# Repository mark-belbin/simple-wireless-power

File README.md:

# Simple Wireless Power System

## Introduction 
This project is a simple two-board wireless power system that can transmit up to 100W at close distances. Originally it was designed as a small part of a subsea resident autonomous underwater vehicle senior design project. The goal was to have a contactless method to charge the vehicles battery in an underwater docking station, versus a contact method like a wetmate connector. This reduces the chance for failure in a harsh ocean environment. Included in this repository are schematics, PCB design files, LTspice simulations, and embedded code.

## Design Topology
At the start of my wireless power investigation, it was initially decided to create a type of "coreless transformer" to keep things simple. This type of design would transfer power by simply placing two identical coils as close as possible to each other. The closer the coils, the higher their mutal inductance and coupling coefficient. The coupling coefficient directly equals the maximum achievable efficiency; k=0.7 would mean 70% efficiency for example. 

> Coreless transformer equivalent circuit.

However, since a lot of work was already being placed into research and simulation anyways, it was decided to try and create a resonant system. Using capactiors, resonant circuits can be created with the inductive transmitter and reciever coils, increasing efficiency accross the wireless link. This is the de facto inductive wireless power transfer method used in industry, and it turned out to be simpler than thought. The topology chosen is called "series-series" resonant inductive wireless power transfer, which means that the compensating capacitors are placed in series with both the transmit and recieve coils. Other topologys exist such as "series-parallel" or "parallel-parallel" which place the capacitors in parallel with the coils as well.

> Series-series topology circuit.

## Hardware
The system consists of a transmitter (TX) PCB and a reciever (RX) PCB. Both are 4 layer 1oz copper boards that are 100x45mm. The designs were completed using KiCAD EDA (http://kicad-pcb.org/), a free and open source PCB design software that is highly recommended. 

### TX Board
The transmitter board's primary purpose is to take a DC input voltage and pass it through a full bridge inverter to create a high frequency sinusoidal voltage. This sinusoidal voltage passes through the compensating capacitors and transmitter coil, and creates an alternating magnetic field that couples to the reciever coil. The H-Bridge is designed around an operating point of 24VDC input, 100kHz switching frequency, and up to 100W of transfer power. The main limiter for power transfer is the rated voltage and current of the coils and compensating capacitors. The MOSFETs of the H-Bridge are over-speced to minimize losses. Short circuit protection circuitry is included on the TX board, since if the TX coil is open-loaded during operation it will appear as a short to the input power supply.

The TX board also has an embedded SAMD21 microntroller which generates the nessecary PWM signal for the gate drivers. Further, the board includes a CAN controller and transceiver so that it could potentially be commanded on/off and relay power transfer telemetry to a remote control computer via CANBus.

### RX Board
The RX board is much simpler than the TX board. It has no microcontroller, and uses passive schottky diodes in a full bridge rectifier configuration to convert the recieved AC voltage back to a usable DC voltage. An simple overvoltage protection scheme is incorporated in the RX board to prevent an overvoltage event downstream. A schmitt trigger circuit watches the output voltage, and if it is too high, connects the output to a bank of bleeder resistors. The extra load on the output subsequently draws down the voltage before it reaches a harmful level. 
                                                                                   

### Key Components

#### Coils
The transmitter and reciever coils are identical. They were sourced on Digi-Key from Wurth Electronics, PN 732-9670-ND. They have an inductance of 5.8uH, and a very low series resistance, allowing for high current rating. I think these are probably the highest current rated coils you can find on Digikey when I selected them! As well, Wurth was kind enough to provide ample documentation for the coils. A key piece of data was a graph of their Quality factor (Q) versus frequency. The higher the quality factor, the better the efficiency. Therefore, since the Q peaked at around 100-101kHz, that was the selected operating frequency for the entire system.

> Coils encased and epoxyed in a custom mount for underwater use in the original AUV application. 

#### Series Capacitors
Four 100nF capacitors were placed in parallel to achieve the desired ~380-400nF series capacitance. Large 2220 package ceramic capacitors were chosen for their desirable low series resistance. The final parts were chosen from Murata Electronics and sourced on Digikey, PN 490-16696-1-ND. These capacitors were compared against others, again looking at their quality factor over frequency. The series capacitors ended up being the weakest link in the system, and would fail on the TX side when delivering over 5-6A. These caps had the best that could be found at the time, but if someone knows of a better or higher current-carrying choice, let me know! 

#### MOSFETs
The MOSFETs chosen are low-loss N-Channel devices. The final parts chosen are from Infineon and sourced on Digi-Key, PN 448-IAUC70N08S5N074ATMA1CT-ND. These FETs were selected for the lowest possible loss, taking into account both resistive and switching losses. 

#### Diodes
The diodes for the full-bridge rectifier were chosen again for as low of loss as possible. Really, the low voltage and high current environment is probably better suited for active rectification, but to keep things simple passive rectification was chosen. The best diodes for this are schottky due to their low forward voltage. The final parts chosen are from ON Semi and sourced from Digi-Key, PN FSV12100VCT-ND. A few different diode models were selected and simulated in the final circuit, and this model ended up producing the lowest loss. 

#### Micro Controller
The chosen microcontroller is the SAMD21G18A, PN ATSAMD21G18A-MF-ND. This is the same microcontroller that is on the Arduino Zero dev board, and our senior design team already knew how to easily program and flash it. Perhaps someone could modify this design and retrofit a more popular microcontroller, like an STM32.

## Software
The current software developed for this project is the embedded code on the TX board's SAMD21 microcontroller. Code was developed using the Arduino IDE for simplicity. A .bin file was generated and then uploaded to the microcontroller using a J-Link EDU programmer. The code is about as simple as it gets, just generating a 50% duty cycle, 100kHz PWM signal. No feedback is incorporated since it is assumed that there is no expected communication between TX and RX boards in the original underwater application. 

## Simulation
The entire end-to-end wireless power system was simulated in LTspice. The simulation aided in component selection, and gave an initial estimate of efficiency greater than 90%. It's hard to say how accurate the simulation is, since it's not clear what coupling factor, k, will be present in a real world system. Any tips on WPT system simulation in LTspice would be greatly appreciated! 

## Testing Results
The system was tested with surpising results. At a gap distance of about 1-2mm, as close as we could get, the system was able to transfer power up to 100W at an efficiency of 81.3%. Testing different frequencies between 95-105kHz did not show any noticeable difference in efficiency. The coils were also submerged in saltwater to check efficiency versus the in-air test. There was no measurable difference in water, salt or fresh.

Another interesting outcome was shown in the thermal images during testing. The hottest components in the system were the series capacitors, reaching upwards of 70C degrees after 5 mins of operation. No heatsink or airflow meant that these are probably worst case numbers, but still perhaps the capacitors could be underspec'd for the application. At 100W delivered, about 20W is lost in the system, and the series capacitors are the only noticeable components that heat up significantly. It's a bit inconcievable that all the 20W is split amongst 8 small capacitors, so I assume that there are some losses in the surrounding air that are radiated away. It's hard to tell, would definitely be open to some insight on this if anyone has encountered this before! 

Efficiency vs coil gap distance measurements were completed with some interesting results. First, efficiency seems to drop linearly from 0-20mm. This is cool since it seems that the resonant effect is indeed working. Normally a magnetic field would decrease with the distance squared, a non-linear relationship. As well, when reaching 20mm or beyond, the TX board was limited by its series current capability. More series current is required in to the transmitter coil to achieve the same power transfer as efficiency drops. The series capacitors on the TX board were the limiter, as they started to fail beyond 6A. A heatsink and forced air could give them a bit of extra capability potentially. I'd be interested in hearing about any better capacitor choices for higher series current while maintaining low loss accross them, or perhaps if a parallel-series or parallel-parallel topology would solve this problem.

## Discussion
This was a fun project and a small part of a much larger senior design project. 80-75% efficiency for 0-5mm coil gap satisfies the original design problem, which was to safely deliver 50W underwater at a 0-5mm gap distance. Always open for discussion or any tips on how this could have been done better. For a future project I'm interested in trying to make a super small low power version that could deliver 5-10W for underwater sensor applications.

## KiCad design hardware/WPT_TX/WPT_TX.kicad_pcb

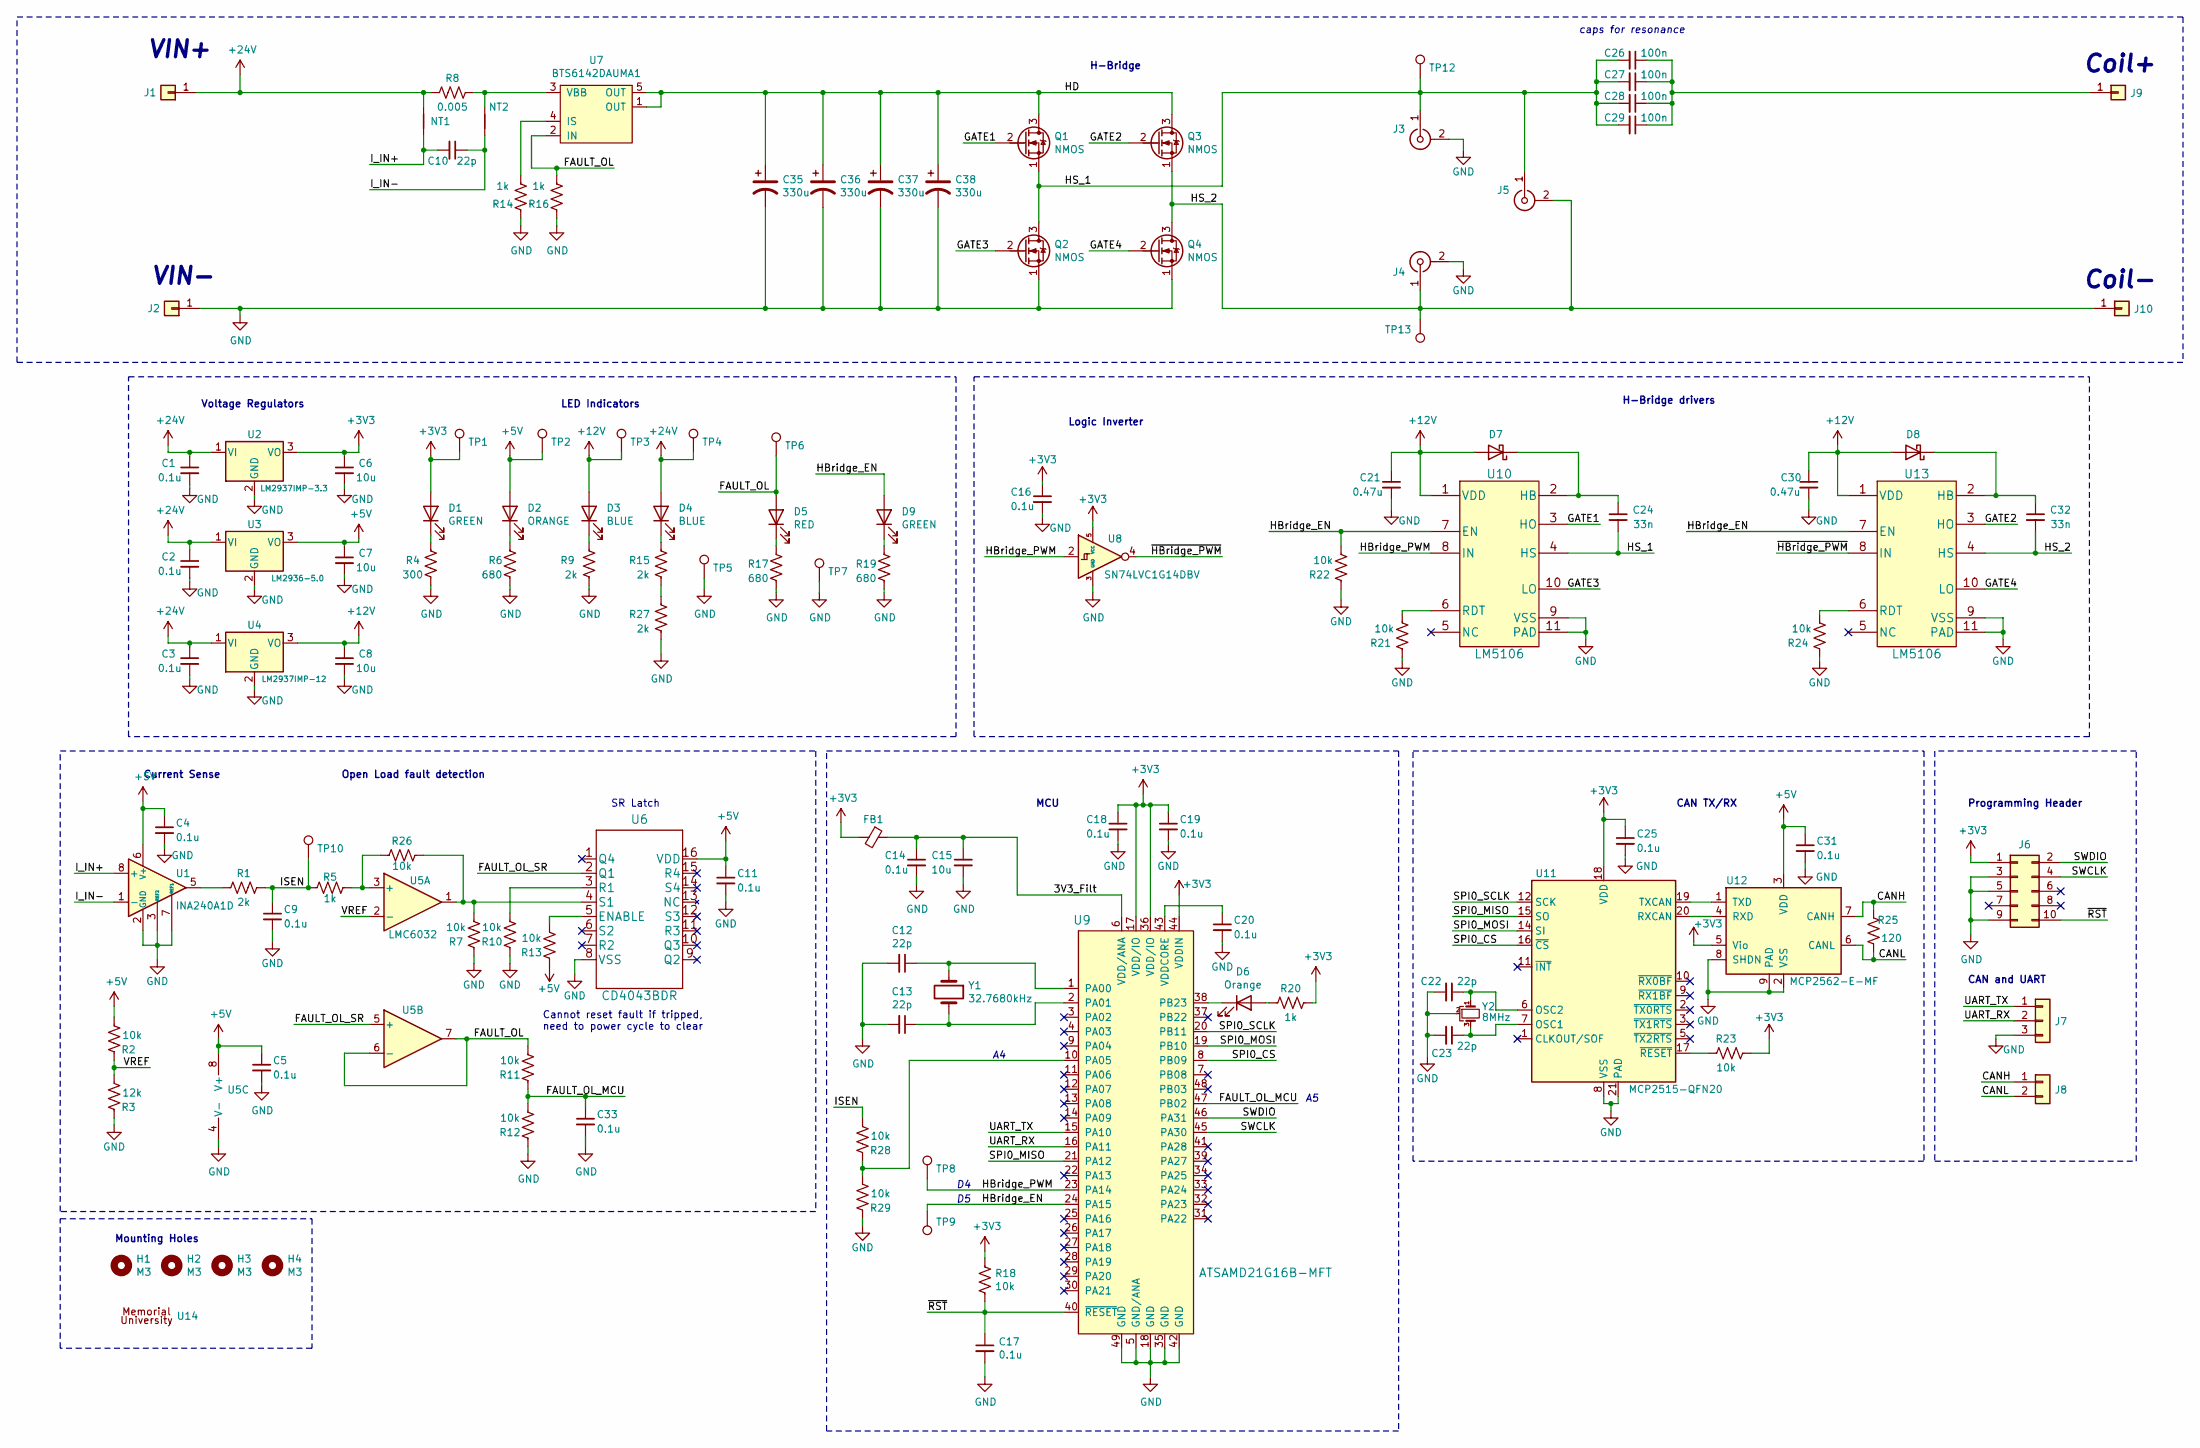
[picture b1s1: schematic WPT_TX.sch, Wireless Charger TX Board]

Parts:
C1, C2, C3: 0.1u; C_0603_1608Metric; Digikey 1276-1941-1-ND
C4, C5, C9, C11, C14, C16, C17, C18, C19, C20, C25, C31, C33: 0.1u; C_0603_1608Metric; Digikey 1276-1258-1-ND
C6, C7, C8: 10u; C_1206_3216Metric; Digikey 1276-6767-1-ND
C10, C12, C13, C22, C23: 22p; C_0603_1608Metric; Digikey 720-VJ0603A220JXBACCT-ND
C15: 10u; C_0603_1608Metric; Digikey 490-7201-1-ND
C21, C30: 0.47u; C_0805_2012Metric; Digikey 478-10438-1-ND
C24, C32: 33n; C_0805_2012Metric; Digikey 445-172691-1-ND
C26, C27, C28, C29: 100n; C_2220_5650Metric; Digikey 490-16696-1-ND
C35, C36, C37, C38: 330u; CP_Elec_10x12.5; Digikey 493-13765-1-ND
D1, D9: GREEN; LED_0805_2012Metric; Digikey 160-1423-1-ND
D2: ORANGE; LED_0805_2012Metric; Digikey 160-1413-1-ND
D3, D4: BLUE; LED_0805_2012Metric; Digikey 160-1579-1-ND
D5: RED; LED_0805_2012Metric; Digikey 475-1415-1-ND
D6: Orange; LED_0805_2012Metric; Digikey 160-1413-1-ND
D7, D8: D_Schottky; D_SOD-323_HandSoldering; Digikey 641-1786-1-ND
FB1: FB; L_0805_2012Metric; Digikey 490-9706-1-ND
H1, H2, H3, H4: M3; MountingHole_3.2mm_M3_DIN965_Pad
J1, J2, J9, J10: Conn_01x01; SolderWirePad_single_SMD_5x10mm
J3, J4, J5: Conn_Coaxial; SMA_Amphenol_901-144_Vertical; Digikey WM17068-ND
J6: Conn_02x05_Odd_Even; PinHeader_2x05_P1.27mm_Vertical; Digikey 1175-1627-ND
J7: Conn_01x03; 70553-03; Digikey WM4154-ND
J8: Conn_01x04; 70553-02; Digikey WM4900-ND
NT1, NT2: Net-Tie_2; NetTie-2_SMD_Pad0.25mm
Q1, Q2, Q3, Q4: NMOS; TDSON-8-1; Digikey 448-IAUC70N08S5N074ATMA1CT-ND
R1, R9, R15, R27: 2k; R_0603_1608Metric; Digikey 541-2790-1-ND
R2, R7, R10, R11, R12, R13, R18, R21, R22, R23, R24, R26, R28, R29: 10k; R_0603_1608Metric; Digikey RHM10KDCT-ND
R3: 12k; R_0603_1608Metric; Digikey P12KDBCT-ND
R4: 300; R_0603_1608Metric; Digikey P300BZCT-ND
R5, R14, R16, R20: 1k; R_0603_1608Metric; Digikey RHM1.0KDCT-ND
R6, R17, R19: 680; R_0603_1608Metric; Digikey RHM680DCT-ND
R8: 0.005; R_2512_Sense; Digikey YAG6124CT-ND
R25: 120; R_0603_1608Metric; Digikey P120BYTR-ND
TP1, TP2, TP3, TP4: TestPoint; TestPoint_Loop_D1.80mm_Drill1.0mm_Beaded; Digikey 36-5000-ND
TP5, TP6, TP7: TestPoint; TestPoint_Loop_D1.80mm_Drill1.0mm_Beaded; Digikey 36-5001-ND
TP8, TP9, TP10, TP12, TP13: TestPoint; TestPoint_Loop_D1.80mm_Drill1.0mm_Beaded; Digikey 36-5117-ND
U1: INA240A1D; SOIC-8_3.9x4.9mm_P1.27mm; Digikey 296-48837-ND
U2: LM2937IMP-3.3; SOT-223-3_TabPin2; Digikey LM2937IMPX-3.3/NOPBCT-ND
U3: LM2936-5.0; SOT-223-3_TabPin2; Digikey 296-37374-1-ND
U4: LM2937IMP-12; SOT-223-3_TabPin2; Digikey LM2937IMP-12/NOPBCT-ND
U5: LMC6032; SOIC-8_3.9x4.9mm_P1.27mm
U6: CD4043BDR; SOIC-16_3.9x9.9mm_P1.27mm; Digikey 296-31496-1-ND
U7: BTS6142DAUMA1; TO-252-4; Digikey BTS6142DAUMA1CT-ND
U8: SN74LVC1G14DBV; TSOT-23-5; Digikey 296-35944-1-ND
U9: ATSAMD21G16B-MFT; QFN-48-1EP_7x7mm_P0.5mm_EP5.6x5.6mm; Digikey ATSAMD21G18A-MF-ND
U10, U13: LM5106; LM5106SD; Digikey LM5106SD/NOPBCT-ND
U11: MCP2515-QFN20; QFN-20-1EP_4x4mm_P0.5mm_EP2.5x2.5mm_ThermalVias; Digikey MCP2515-E/ML-ND
U12: MCP2562-E-MF; DFN-8-1EP_3x3mm_P0.65mm_EP1.55x2.4mm; Digikey MCP2562-E/MF-ND
U14: Munlogo; MUNLOGO
Y1: 32.7680kHz; Crystal_SMD_3215-2pin_3.2x1.5mm; Digikey ‎XC1656CT-ND‎
Y2: 8MHz; OSCCC320X250; Digikey 2151-RH100-8.000-20-3050-EXT-TRCT-ND

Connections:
+3V3: C6.1, C16.1, C18.1, C19.1, C25.1, D1.2 (A), FB1.2, J6.1, R18.1, R20.1, R23.1, TP1.1, U2.3 (VO), U8.5 (VCC), U9.17 (VDD/IO), U9.36 (VDD/IO), U9.44 (VDDIN), U11.18 (VDD), U12.5 (Vio)
+5V: C4.1, C5.1, C7.1, C11.1, C31.1, D2.2 (A), R2.2, R13.1, TP2.1, U1.6 (V+), U3.3 (VO), U5.8 (V+), U6.16 (VDD), U12.3 (VDD)
+12V: C8.1, C21.1, C30.1, D3.2 (A), D7.2 (A), D8.2 (A), TP3.1, U4.3 (VO), U10.1 (VDD), U13.1 (VDD)
+24V: C1.1, C2.1, C3.1, D4.2 (A), J1.1, NT1.1, R8.2, TP4.1, U2.1 (VI), U3.1 (VI), U4.1 (VI)
/3V3_Filt: C14.1, C15.1, FB1.1, U9.6 (VDD/ANA)
/CANH: J8.1, R25.2, U12.7 (CANH)
/CANL: J8.2, R25.1, U12.6 (CANL)
/FAULT_OL: D5.2 (A), R11.2, R16.2, TP6.1, U5.6 (-), U5.7, U7.2 (IN)
/FAULT_OL_MCU: C33.1, R11.1, R12.2, U9.47 (PB02)
/FAULT_OL_SR: U5.5 (+), U6.2 (Q1)
/GATE1: Q1.2 (G), U10.3 (HO)
/GATE2: Q3.2 (G), U13.3 (HO)
/GATE3: Q2.2 (G), U10.10 (LO)
/GATE4: Q4.2 (G), U13.10 (LO)
/HBridge_EN: D9.2 (A), R22.2, TP9.1, U9.24 (PA15), U10.7 (EN), U13.7 (EN)
/HBridge_PWM: TP8.1, U8.2, U9.23 (PA14), U10.8 (IN)
/HD: C35.1, C36.1, C37.1, C38.1, Q1.3 (D), Q3.3 (D), U7.1 (OUT), U7.5 (OUT)
/HS_1: C24.2, C26.2, C27.2, C28.2, C29.2, J3.1 (In), J5.1 (In), Q1.1 (S), Q2.3 (D), TP12.1, U10.4 (HS)
/HS_2: C32.2, J4.1 (In), J5.2 (Ext), J10.1, Q3.1 (S), Q4.3 (D), TP13.1, U13.4 (HS)
/ISEN: C9.1, R1.1, R5.2, R28.2, TP10.1
/I_IN+: C10.2, NT1.2, U1.8 (+)
/I_IN-: C10.1, NT2.1, U1.1 (-)
/SPI0_CS: U9.8 (PB09), U11.16 (~CS)
/SPI0_MISO: U9.21 (PA12), U11.15 (SO)
/SPI0_MOSI: U9.19 (PB10), U11.14 (SI)
/SPI0_SCLK: U9.20 (PB11), U11.12 (SCK)
/SWCLK: J6.4, U9.45 (PA30)
/SWDIO: J6.2, U9.46 (PA31)
/UART_RX: J7.2, U9.16 (PA11)
/UART_TX: J7.1, U9.15 (PA10)
/VREF: R2.1, R3.2, U5.2 (-)
/~HBridge_PWM~: U8.4, U13.8 (IN)
/~RST~: C17.1, J6.10, R18.2, U9.40 (~RESET)
GND: C1.2, C2.2, C3.2, C4.2, C5.2, C6.2, C7.2, C8.2, C9.2, C11.2, C12.2, C13.2, C14.2, C15.2, C16.2, C17.2, C18.2, C19.2, C20.2, C21.2, C22.2, C23.2, C25.2, C30.2, C31.2, C33.2, C35.2, C36.2, C37.2, C38.2, J2.1, J3.2 (Ext), J4.2 (Ext), J6.3, J6.5, J6.9, J7.3, Q2.1 (S), Q4.1 (S), R3.1, R4.1, R6.1, R7.1, R9.1, R10.1, R12.1, R14.1, R16.1, R17.1, R19.1, R21.1, R22.1, R24.1, R27.1, R29.1, TP5.1, TP7.1, U1.2 (GND), U1.3 (REF2), U1.4 (GND), U1.7 (REF1), U2.2 (GND), U3.2 (GND), U4.2 (GND), U5.4 (V-), U6.8 (VSS), U8.3 (GND), U9.5 (GND/ANA), U9.18 (GND), U9.35 (GND), U9.42 (GND), U9.49 (GND), U10.9 (VSS), U10.11 (PAD), U11.8 (VSS), U11.21 (PAD), U12.2 (VSS), U12.8 (SHDN), U12.9 (PAD), U13.9 (VSS), U13.11 (PAD), Y2.2
unnamed: C12.1, U9.1 (PA00), Y1.1
unnamed: C13.1, U9.2 (PA01), Y1.2
unnamed: C20.1, U9.43 (VDDCORE)
unnamed: C22.1, U11.6 (OSC2), Y2.1
unnamed: C23.1, U11.7 (OSC1), Y2.3
unnamed: C24.1, D7.1 (K), U10.2 (HB)
unnamed: C26.1, C27.1, C28.1, C29.1, J9.1
unnamed: C32.1, D8.1 (K), U13.2 (HB)
unnamed: D1.1 (K), R4.2
unnamed: D2.1 (K), R6.2
unnamed: D3.1 (K), R9.2
unnamed: D4.1 (K), R15.2
unnamed: D5.1 (K), R17.2
unnamed: D6.1 (K), U9.38 (PB23)
unnamed: D6.2 (A), R20.2
unnamed: D9.1 (K), R19.2
unnamed: NT2.2, R8.1, U7.3 (VBB)
unnamed: R1.2, U1.5
unnamed: R10.2, U6.3 (R1)
unnamed: R13.2, U6.5 (ENABLE)
unnamed: R14.2, U7.4 (IS)
unnamed: R15.1, R27.2
unnamed: R21.2, U10.6 (RDT)
unnamed: R23.2, U11.17 (~RESET)
unnamed: R24.2, U13.6 (RDT)
unnamed: R7.2, R26.1, U5.1, U6.4 (S1)
unnamed: R5.1, R26.2, U5.3 (+)
unnamed: R28.1, R29.2, U9.10 (PA05)
unnamed: U11.19 (TXCAN), U12.1 (TXD)
unnamed: U11.20 (RXCAN), U12.4 (RXD)

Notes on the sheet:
Coil+
VIN+
VIN-
Coil-
caps for resonance
Current Sense
Open Load fault detection
Voltage Regulators
MCU
CAN TX/RX
H-Bridge
H-Bridge drivers
Cannot reset fault if tripped, need to power cycle to clear
SR Latch
Logic Inverter
Programming Header
CAN and UART
LED Indicators
Mounting Holes

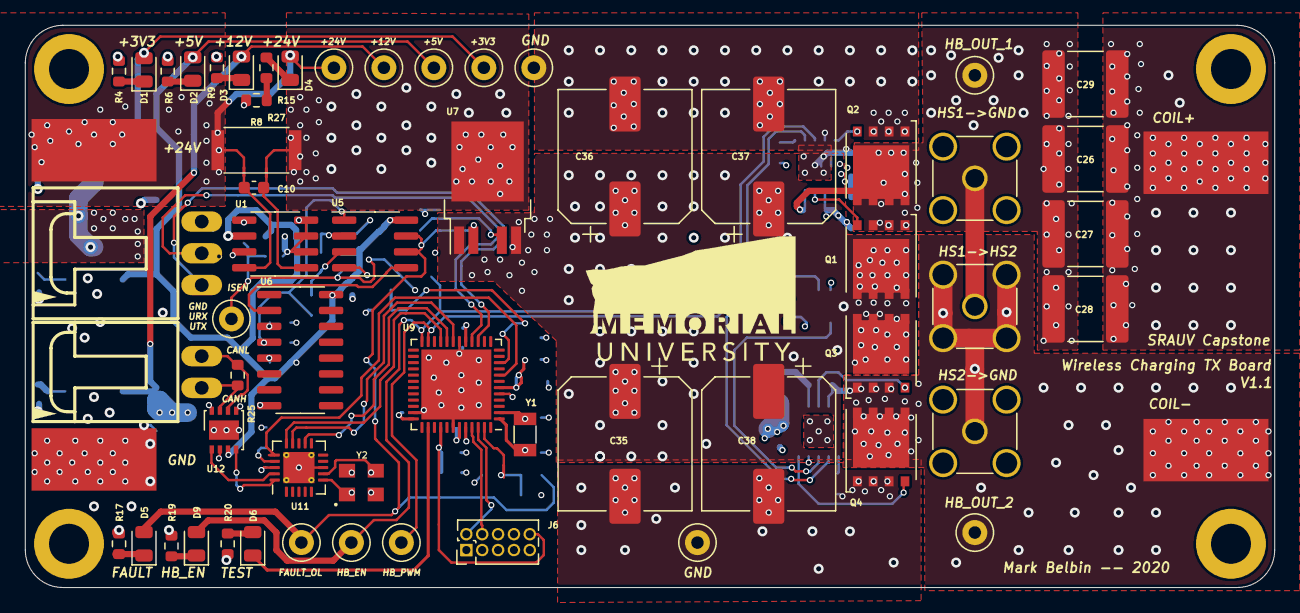
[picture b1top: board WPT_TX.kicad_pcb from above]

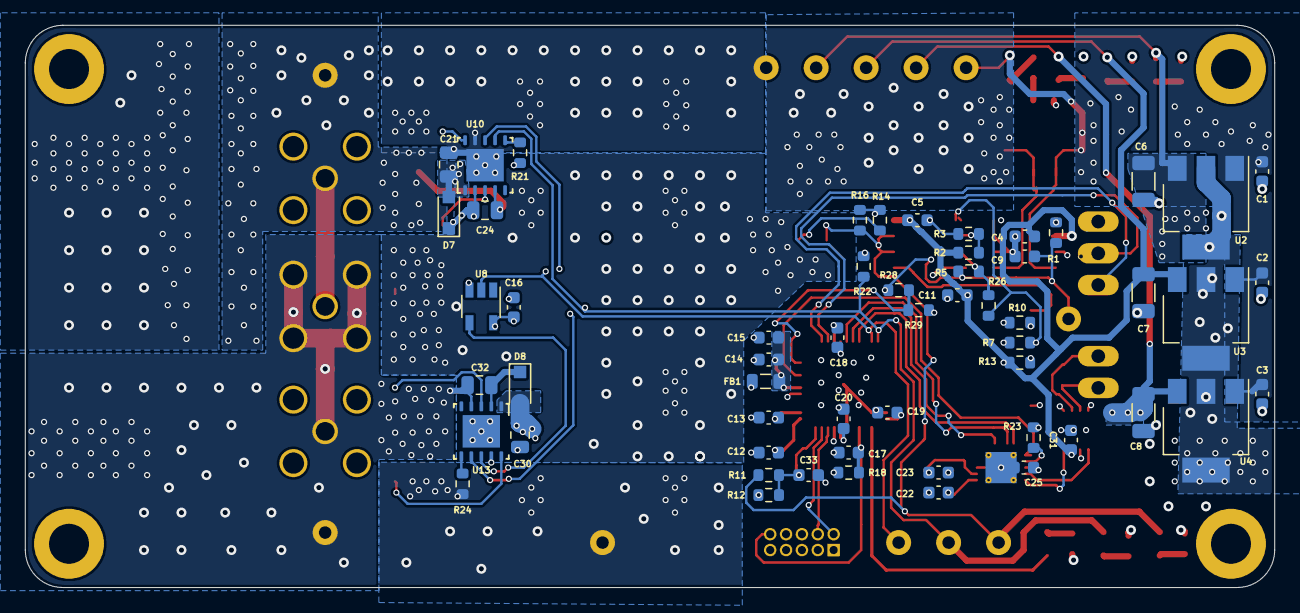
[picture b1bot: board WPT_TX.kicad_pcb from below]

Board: 4 copper layers, 100.0 x 45.0 mm, 124 parts (56 on the bottom side), 64 nets.

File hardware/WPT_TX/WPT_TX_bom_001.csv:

Component,Description,Part,References,Value,Footprint,Quantity Per PCB,Datasheet,Digikey
1,"Unpolarized capacitor, small symbol",C_Small,C1 C2 C3 C4 C5 C9 C11 C14 C16 C17 C18 C19 C20 C25 C31 C33,0.1u,C_0603_1608Metric,16,~,1276-1941-1-ND 1276-1258-1-ND
2,"Unpolarized capacitor, small symbol",C_Small,C21 C30,0.47u,C_0805,2,~,478-10438-1-ND
3,"Unpolarized capacitor, small symbol",C_Small,C26 C27 C28 C29,100n,C_2220,4,~,490-16696-1-ND
4,"Unpolarized capacitor, small symbol",C_Small,C15,10u,C_0603_1608Metric,1,~,490-7201-1-ND
5,"Unpolarized capacitor, small symbol",C_Small,C6 C7 C8,10u,C_1206,3,~,1276-6767-1-ND
6,"Unpolarized capacitor, small symbol",C_Small,C10 C12 C13 C22 C23,22p,C_0603_1608Metric,5,~,720-VJ0603A220JXBACCT-ND
7,"Unpolarized capacitor, small symbol",C_Small,C24 C32,33n,C_0805,2,~,445-172691-1-ND
8,Light emitting diode,LED,D3 D4,BLUE,LED_0805_2012Metric,2,~,160-1579-1-ND
9,Schottky diode,D_Schottky,D7 D8,D_Schottky,D_SMA,2,~,SS16T3GOSCT-ND
10,Light emitting diode,LED,D1 D9,GREEN,LED_0805_2012Metric,2,~,160-1423-1-ND
11,Light emitting diode,LED,D2 D6,ORANGE,LED_0805_2012Metric,2,~,160-1413-1-ND
12,Light emitting diode,LED,D5,RED,LED_0805_2012Metric,1,~,475-1415-1-ND
13,"Ferrite bead, small symbol",Ferrite_Bead_Small,FB1,FB,L_0805_2012Metric,1,~,490-9706-1-ND
14,"Generic connector, single row, 01x01, script generated (kicad-library-utils/schlib/autogen/connector/)",Conn_01x01,J1 J2 J9 J10,Conn_01x01,SolderWirePad_single_SMD_5x10mm,4,~,
15,"Generic connector, single row, 01x03, script generated (kicad-library-utils/schlib/autogen/connector/)",Conn_01x03,J7,Conn_01x03,70553-03,1,~,WM4154-ND
16,"Generic connector, single row, 01x02, script generated (kicad-library-utils/schlib/autogen/connector/)",Conn_01x02,J8,Conn_01x04,70553-02,1,~,WM4900-ND
17,"Generic connector, double row, 02x05, odd/even pin numbering scheme (row 1 odd numbers, row 2 even numbers), script generated (kicad-library-utils/schlib/autogen/connector/)",Conn_02x05_Odd_Even,J6,Conn_02x05_Odd_Even,Pin_Header_Straight_2x05_Pitch1.27mm,1,~,1175-1627-ND
18,"coaxial connector (BNC, SMA, SMB, SMC, Cinch/RCA, ...)",Conn_Coaxial,J3 J4 J5,Conn_Coaxial,SMA_Amphenol_901-144_Vertical,3, ~,WM17068-ND
19,"Net tie, 2 pins",Net-Tie_2,NT1 NT2,Net-Tie_2,NetTie-2_SMD_Pad0.25mm,2,~,
20,"N-MOSFET transistor, source/gate/drain",Q_NMOS_SGD,Q1 Q2 Q3 Q4,NMOS,TDSON-8-1,4,https://www.infineon.com/dgdl/Infineon-IAUC70N08S5N074-DS-v0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,448-IAUC70N08S5N074ATMA1CT-ND
21,"Resistor, US symbol",R_US,R8,0.005,R_2512_Sense,1,~,YAG6124CT-ND
22,"Resistor, US symbol",R_US,R3 R7 R10 R11 R12 R13 R18 R21 R22 R23 R24 R26,10k,R_0603_1608Metric,12,~,RHM10KDCT-ND
23,"Resistor, US symbol",R_US,R25,120,R_0603_1608Metric,1,~,P120BYTR-ND
24,"Resistor, US symbol",R_US,R9 R14 R16 R20,1k,R_0603_1608Metric,4,~,RHM1.0KDCT-ND
25,"Resistor, US symbol",R_US,R1 R15,2k,R_0603_1608Metric,2,~,541-2790-1-ND
26,"Resistor, US symbol",R_US,R4,330,R_0603_1608Metric,1,~,RHM330DCT-ND
27,"Resistor, US symbol",R_US,R6 R17 R19,680,R_0603_1608Metric,3,~,RHM680DCT-ND
28,"Resistor, US symbol",R_US,R2 R5,79.6k,R_0603_1608Metric,2,~,13-RT0603BRD0779K6LCT-ND
29,IC MCU 32BIT 64KB FLASH 48QFN,ATSAMD21G16B-MFT,U9,ATSAMD21G16B-MFT,TQFP-48_7x7mm,1,http://www.microchip.com/mymicrochip/filehandler.aspx?ddocna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,ATSAMD21G18A-MF-ND
30,,BTS6142DAUMA1,U7,BTS6142DAUMA1,TO-252-4,1,https://www.infineon.com/dgdl/Infineon-BTS6142D-DS-v01_01-EN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,BTS6142DAUMA1CT-ND
31,,CD4043BDR,U6,CD4043BDR,SOIC-16_3.9x9.9mm_Pitch1.27mm,1,,296-31496-1-ND
32,"High- and Low-Side, Bidirectional, Zero-Drift, Current-Sense Amplifier With Enhanced PWM Rejection, 20V/V, SOIC-8",INA240A1D,U1,INA240A1D,SOIC-8_3.9x4.9mm_P1.27mm,1,http://www.ti.com/lit/ds/symlink/ina240.pdf,296-48837-ND
33,"50mA Ultra-Low Quiescent Current LDO Voltage Regulator, 5.0V fixed output, TO-252/SOT-223",LM2936-5.0,U3,LM2936-5.0,SOT-223-3_TabPin2,1,http://www.ti.com/lit/ds/symlink/lm2936.pdf,296-37374-1-ND
34,"500-mA Low Dropout Regulator, SOT-223",LM2937xMP,U4,LM2937IMP-12,SOT-223-3_TabPin2,1,http://www.ti.com/lit/ds/symlink/lm2937.pdf,LM2937IMP-12/NOPBCT-ND
35,"500-mA Low Dropout Regulator, SOT-223",LM2937xMP,U2,LM2937IMP-3.3,SOT-223-3_TabPin2,1,http://www.ti.com/lit/ds/symlink/lm2937.pdf,LM2937IMPX-3.3/NOPBCT-ND
36,,LM5106SD_NOPB,U10 U13,LM5106,LM5106SD,2,,LM5106SD/NOPBCT-ND
37,"Precision CMOS Dual Operational Amplifier, DIP-8/SOIC-8",LMC6082,U5,LMC6032,SOIC-8_3.9x4.9mm_Pitch1.27mm,1,http://www.ti.com/lit/ds/symlink/lmc6082.pdf,296-49646-1-ND
38,,MCP2515-QFN20,U11,MCP2515-QFN20,TSSOP-20_4.4x6.5mm_P0.65mm,1,,MCP2515-E/ML-ND
39,"High-Speed CAN Transceiver, 1Mbps, 5V supply, Vio pin, -40C to +125C, DFN-8",MCP2562-E-MF,U12,MCP2562-E-MF,DFN-8-1EP_3x3mm_P0.65mm_EP1.55x2.4mm,1,http://ww1.microchip.com/downloads/en/DeviceDoc/25167A.pdf,MCP2562-E/MF-ND
40,"Single Schmitt-Trigger Inverter, SOT-23",SN74LVC1G14DBV,U8,SN74LVC1G14DBV,SOT-23-5,1,http://www.ti.com/lit/ds/symlink/sn74lvc1g14.pdf,296-35944-1-ND
41,Two pin crystal,Crystal,Y1,32.7680kHz,Crystal_SMD_3215-2pin_3.2x1.5mm,1,~,887-2605-1-ND
42,"Three pin crystal, GND on pin 2, small symbol",Crystal_GND2_Small,Y2,8MHz,OSCCC320X250,1,~,2151-RH100-8.000-20-3050-EXT-TRCT-ND





Component Groups:,42
Component Count:,100
Fitted Components:,100
Number of PCBs:,1
Total components:,100
Schematic Version:,001
Schematic Date:,2020-11-08
PCB Variant:,[u'default']
BoM Date:,2020-11-08 10:35:57 PM
Schematic Source:,D:\AUV Capstone\AUV-Senior-Design\Mark\WPT_TX\WPT_TX.sch
KiCad Version:,Eeschema (5.1.8)-1

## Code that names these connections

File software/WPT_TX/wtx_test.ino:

const int HBridge_PWM = 2; //Add pins here
const int HBridge_EN = 5;
const int ISEN = A4;

float current = 0;

void setup() {
  pinMode(HBridge_PWM, OUTPUT);
  pinMode(HBridge_EN, OUTPUT);
  
  delay(1000);  //Wait after powering on.

  /*//Optional Printing
  Serial.println("Starting WTX in 3");
  delay(1);  
  Serial.print("...2");
  delay(1);  
  Serial.print("...1");
  delay(1);  
  Serial.print("....POW");*/

  digitalWrite(HBridge_EN, HIGH);
  tone(HBridge_PWM, 100000); // 100kHz default
}

void loop() {
 //Do Nothing
}

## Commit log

2021-05-23 Added Original Files
    - Transferred over files from original senior design project repo.
    - Organized files into hardware, software, and simulation folders.
2021-05-23 Added Initial Readme Text
    - Added some preliminary text and structure.
    - Will add photos and more text later.
2021-05-23 Text Update
    More substantial design details added in the README.
2021-05-23 Schematics
    - Add sch pdfs to additional folder in hardware for readability.
2021-05-23 Images and Reference
    - Added images for readme
    - Added papers and other reference documents
2021-05-23 Added Pictures to README
    - Added pictures to README for context
2021-05-23 More README Images
    - Added topology circuit images.
2021-05-23 Added circuit images
    - Topology circuit images
2021-05-23 Schematic images
    - Added snips of each board schematic
2021-05-23 More Images
    - Schematic images
2021-05-23 Added thermal image
    - Missed the thermal shot of the caps
2021-05-23 Grammar Fixes
    - Probably will be more of these
2021-05-25 Schematic Updates
    - Removed "HD" net label from HB pins on gate drivers. This resulted in a critical failure on the original board and was fixed with a bodge.
    - Added an extra voltage divider to ISEN input to reduce chance of 5V overvolt scenario.
    - Increased series resistor value for blue LEDs by a factor of 2. Waaaay too bright.
    - Decreased series resistor for 3V3 LED indicator, too dim.
2021-05-25 Updated PCB
    - Added four extra resistors from schematic changes to PCB.
    - Removed HD connections in gate driver layout.
    - Regenerated gerbers
2021-06-08 Testing
    - Tested system at various gap sizes and frequencies.
    - Exported binaries for each freq. test.
    - Updated software folder structure.
2021-06-08 Added Gap Test Image
    - Pretty cool shot
2021-06-08 Added Gap Graph
    - Added pic of measured efficiency vs coil gap.
2021-06-08 Updated README
    - Added updated content based on coil gap measurements.

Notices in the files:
parts and their libraries:
Copyright 2016 Accelerated Designs. All rights reserved.
